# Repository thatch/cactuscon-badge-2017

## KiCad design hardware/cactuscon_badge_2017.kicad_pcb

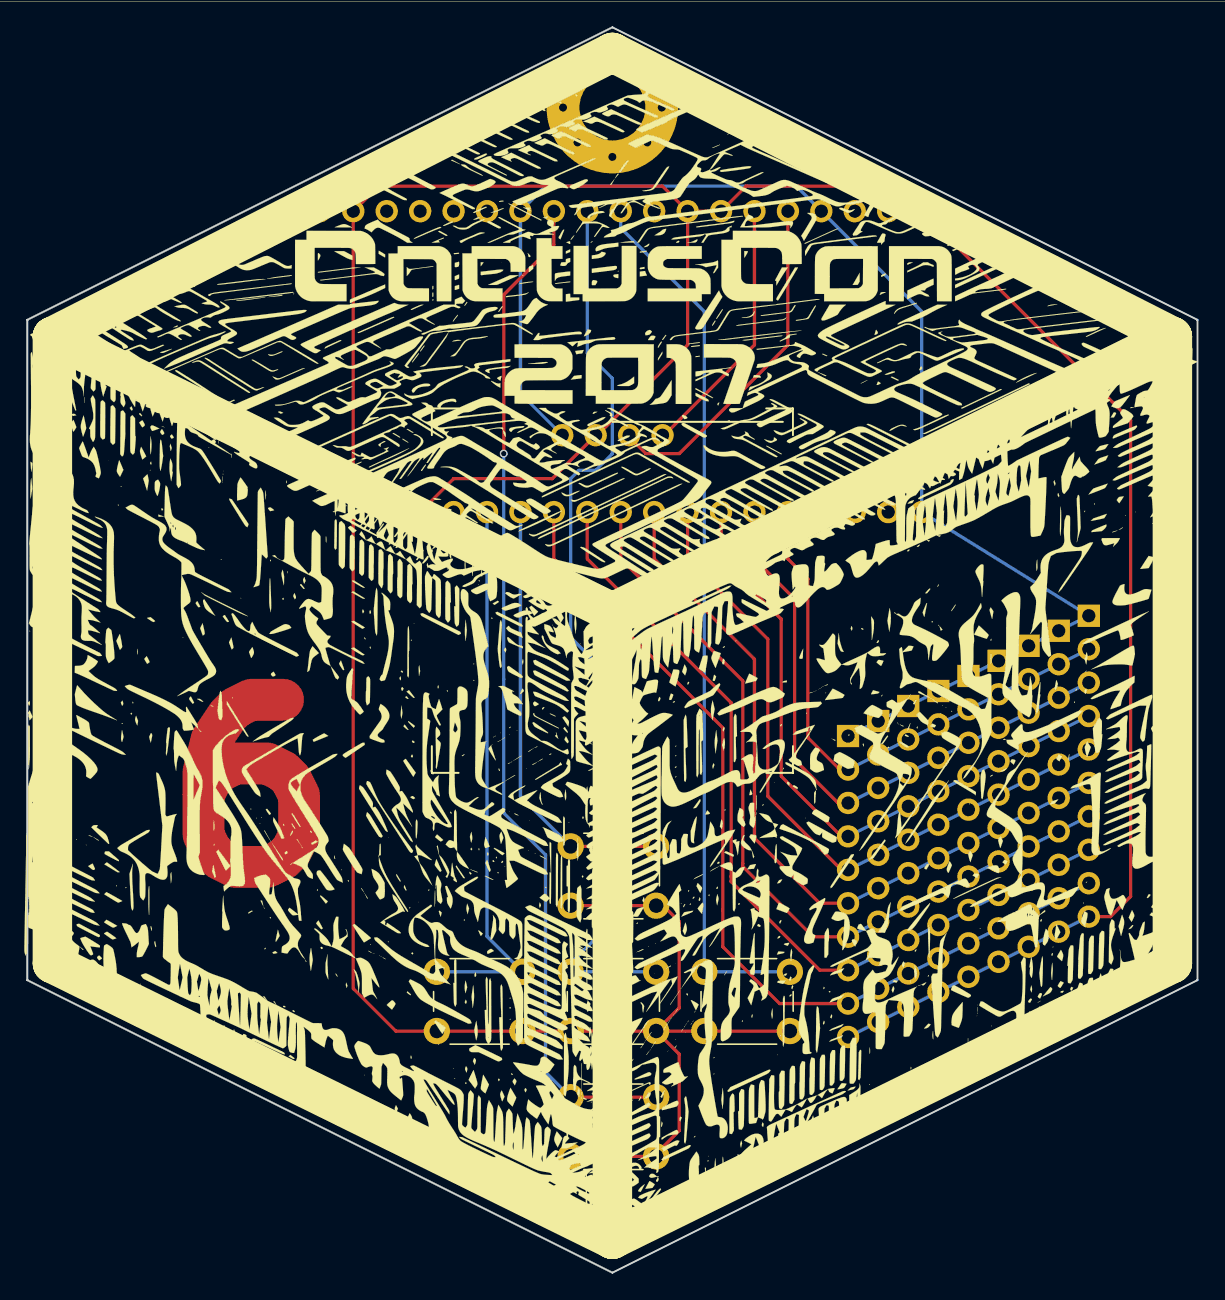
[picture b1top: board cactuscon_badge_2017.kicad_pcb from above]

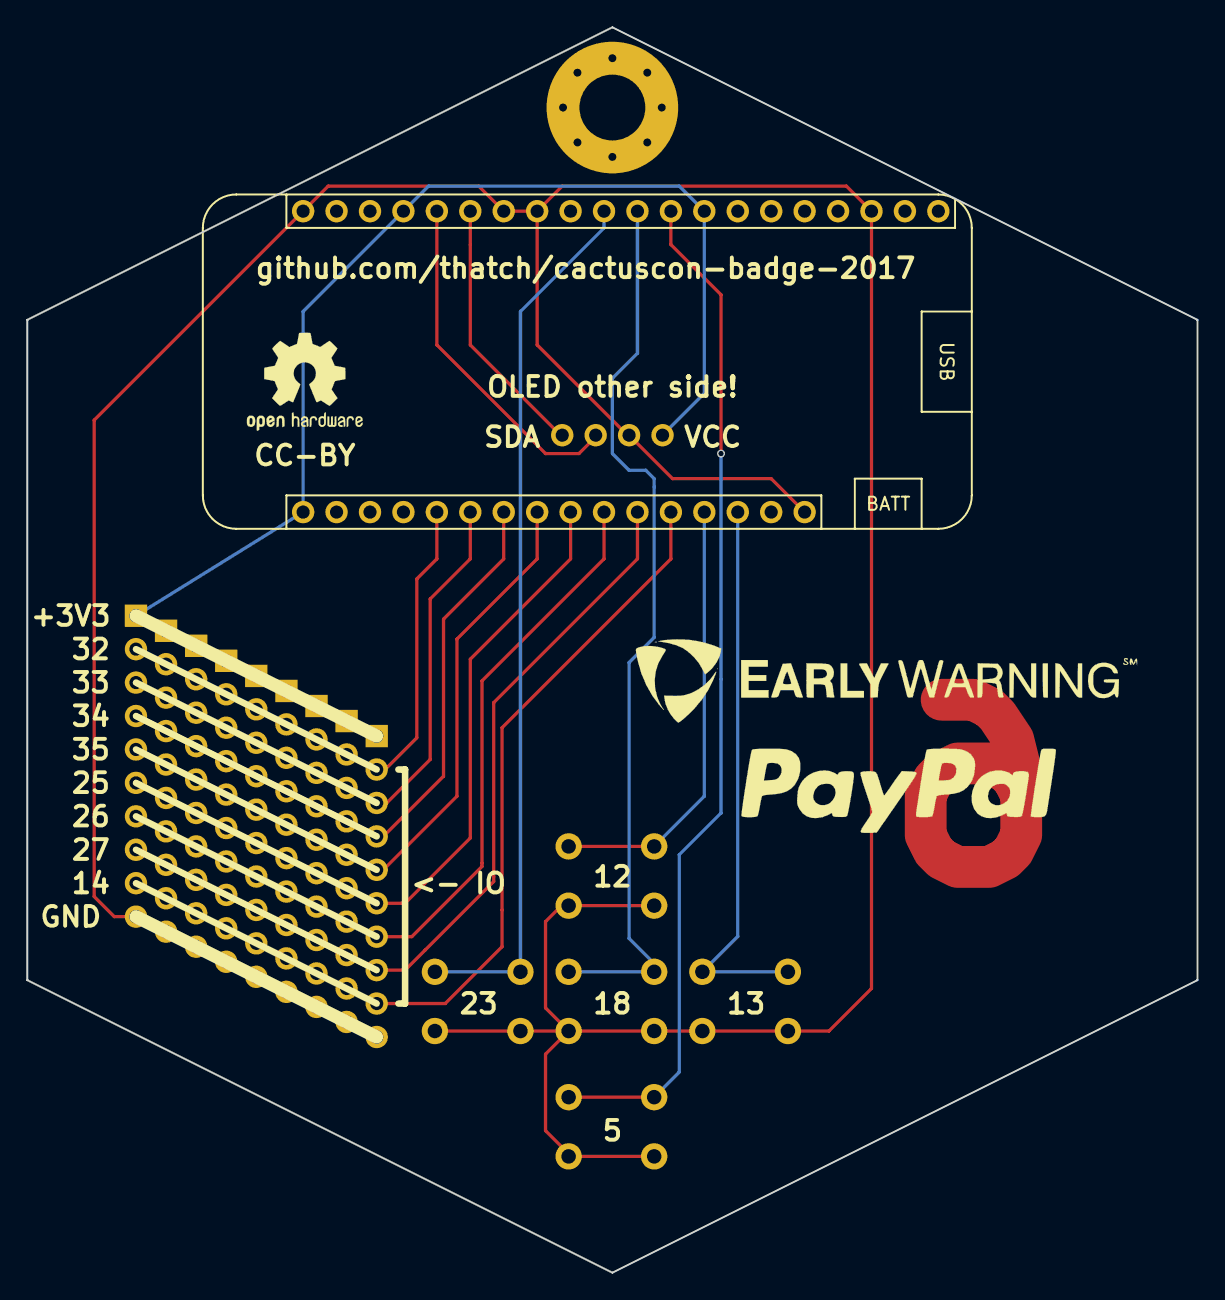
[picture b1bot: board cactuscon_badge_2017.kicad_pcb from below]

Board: 2 copper layers, 88.9 x 94.6 mm, 20 parts (3 on the bottom side), 17 nets.

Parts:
J1: CONN_01X01; MountingHole_5mm_Pad_Via
J2, J3, J4, J6, J7, J8, J9, J10, J11: CONN_01X10; 10Pin_NoSilk
J5: CONN_01X04; SMALL_OLED
J12: Graphic; CactusCon_Full_Badge
J13: Partners; Partner_Logos
J14: OSHW; OSHW-Logo2_9.8x8mm_SilkScreen
M1: LOLIN32
SW1, SW2, SW3, SW4, SW5: SW_Push; SW_PUSH_6mm

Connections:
DN: M1.28, SW4.1
GND: J2.10, J3.10, J4.10, J5.2, J6.10, J7.10, J8.10, J9.10, J10.10, J11.10, M1.16, M1.17, M1.23, M1.24, M1.34, SW1.2, SW2.2, SW3.2, SW4.2, SW5.2
LT: M1.14, SW1.1
unnamed: J2.1, J3.1, J4.1, J5.1, J6.1, J7.1, J8.1, J9.1, J10.1, J11.1, M1.1, M1.20, M1.29
ROW2: J2.2, J3.2, J4.2, J6.2, J7.2, J8.2, J9.2, J10.2, J11.2, M1.5
ROW3: J2.3, J3.3, J4.3, J6.3, J7.3, J8.3, J9.3, J10.3, J11.3, M1.6
ROW4: J2.4, J3.4, J4.4, J6.4, J7.4, J8.4, J9.4, J10.4, J11.4, M1.7
ROW5: J2.5, J3.5, J4.5, J6.5, J7.5, J8.5, J9.5, J10.5, J11.5, M1.8
ROW6: J2.6, J3.6, J4.6, J6.6, J7.6, J8.6, J9.6, J10.6, J11.6, M1.9
ROW7: J2.7, J3.7, J4.7, J6.7, J7.7, J8.7, J9.7, J10.7, J11.7, M1.10
ROW8: J2.8, J3.8, J4.8, J6.8, J7.8, J8.8, J9.8, J10.8, J11.8, M1.11
ROW9: J2.9, J3.9, J4.9, J6.9, J7.9, J8.9, J9.9, J10.9, J11.9, M1.12
RT: M1.26, SW5.1
SCL: J5.3, M1.21
SDA: J5.4, M1.22
SEL: M1.27, SW3.1
UP: M1.13, SW2.1

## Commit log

2017-09-07 Initial commit for badge
2017-09-07 Add README
2017-09-13 Update art, layout, i2c pins, and fix stray trace
2017-09-13 Update submodule for "%TF" filter
2017-09-13 Update front render
2017-09-13 Add repo, partner logos, proto traces to back
2017-09-13 Add OLED warning/pinout
2017-09-13 Enlarge module holes, note IO side, update renders

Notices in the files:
hardware/cactuscon_badge_2017.kicad_pcb:
CC-BY
